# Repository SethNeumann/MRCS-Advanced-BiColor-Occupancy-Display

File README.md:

# REPO NAME:     MRCS-Advanced-BiColor-Occupancy-Display

## License: Creative Commons Attribution-NonCommercial-ShareAlike

The original board, which I designed for Allison Dendy had a pull up SIP (4.7K) and second SIP (nominally 470 ohms) on the common anode to limit
current. Depending on the 3 lead Red/Green LED used the Red was significantly brighter than the Green. Green/Red brightness is always an issue as 
about 20% of males have some red/green color weakness, so adjustment is very individual.

This version has an additional DIP resistor pack in series with the Red leads to further limit the Red brigtness. I used A 220 ohm SIP for the common
anode and 1K for the red. This made the Jameco 2266591 LED appear about as bright on each side to me.

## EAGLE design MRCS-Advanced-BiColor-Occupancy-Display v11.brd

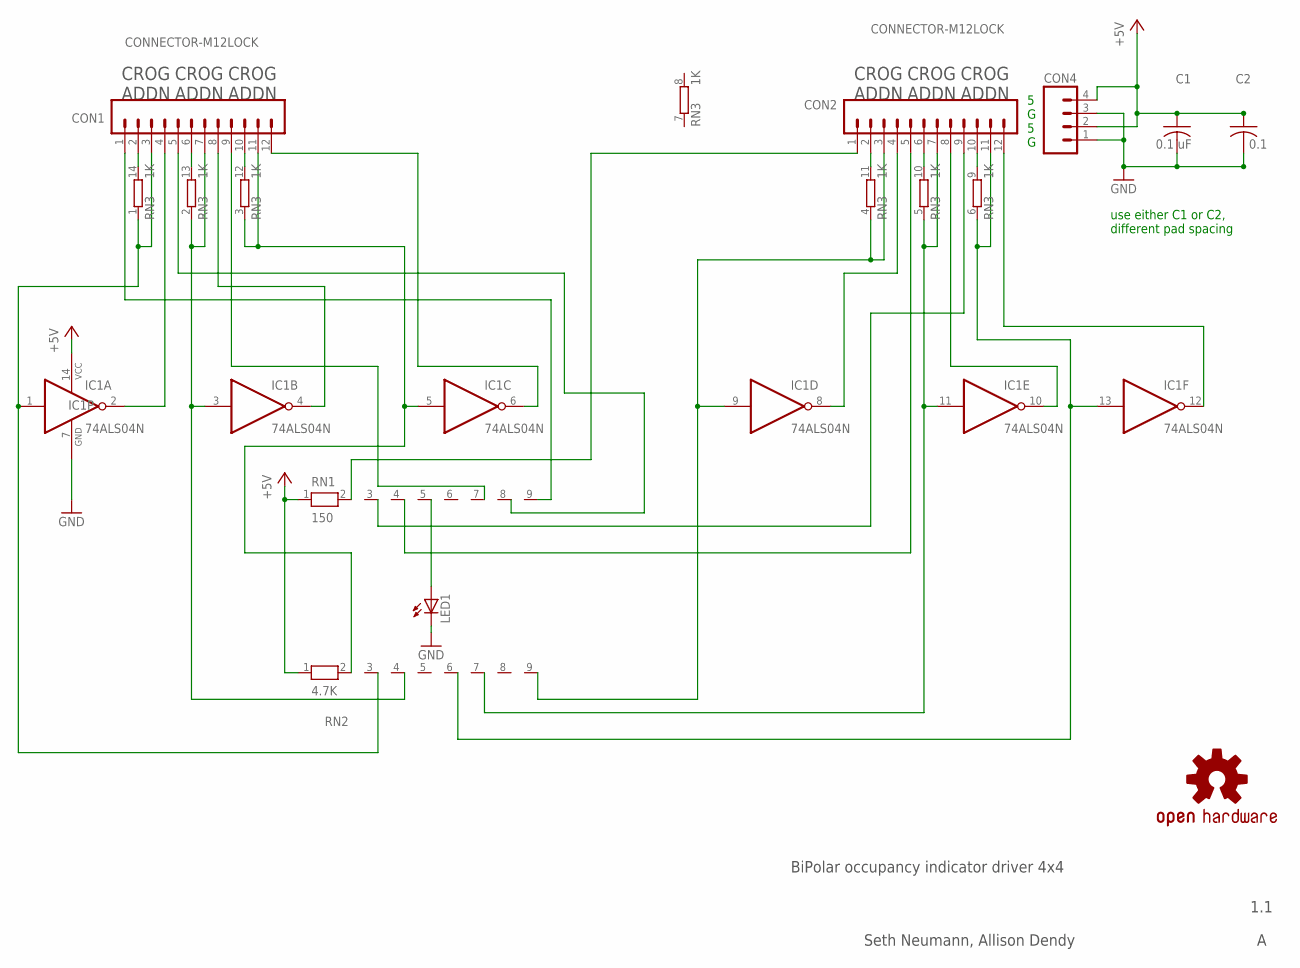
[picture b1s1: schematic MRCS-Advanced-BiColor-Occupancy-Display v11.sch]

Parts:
C1: 0.1 uF; C-PTH-0.100
C2: 0.1; C050-024X044
CON1, CON2: CONNECTOR-M12LOCK; 1X12_LOCK
CON4: CONNECTOR-M04SCREW; SCREWTERMINAL-3.5MM-4
IC1: 74ALS04N; DIL14
LED1: LEDLED3MM; LED3MM
OSHW1: DOC-OSHW-LOGO-M; OSHW-LOGO-M
RN1: 150; RN-9
RN2: 4.7K; RN-9
RN3: 1K; DIL14

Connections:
GND: C1.2, C2.2, CON4.1, CON4.3, IC1.7 (GND), LED1.K (C)
unnamed: CON1.2, RN3.14 (2)
unnamed: CON1.11, IC1.5 (I), RN2.2, RN3.3 (1)
unnamed: CON1.1, RN1.9
unnamed: CON1.4, IC1.2 (O)
unnamed: CON1.7, IC1.3 (I), RN2.4, RN3.2 (1)
unnamed: CON1.12, IC1.6 (O)
unnamed: CON1.8, IC1.4 (O)
unnamed: CON1.5, RN1.8
unnamed: CON2.3, IC1.9 (I), RN2.9, RN3.4 (1)
unnamed: CON1.9, RN1.7
unnamed: CON2.8, IC1.10 (O)
unnamed: CON2.12, IC1.12 (O)
unnamed: CON2.4, IC1.8 (O)
unnamed: CON2.1, RN1.2
unnamed: CON2.5, RN1.4
unnamed: CON1.3, IC1.1 (I), RN2.3, RN3.1
unnamed: LED1.A, RN1.5
unnamed: CON2.7, IC1.11 (I), RN2.7, RN3.5 (1)
unnamed: CON2.9, RN1.3
unnamed: CON2.11, IC1.13 (I), RN2.6, RN3.6 (1)
unnamed: CON1.6, RN3.13 (2)
unnamed: CON1.10, RN3.12 (2)
unnamed: CON2.2, RN3.11 (2)
unnamed: CON2.6, RN3.10 (2)
unnamed: CON2.10, RN3.9 (2)
VCC: C1.1, C2.1, CON4.2, CON4.4, IC1.14 (VCC), RN1.1, RN2.1

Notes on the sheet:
BiPolar occupancy indicator driver 4x4
1.1
Seth Neumann, Allison Dendy
CROG ADDN
5 G 5 G
use either C1 or C2, different pad spacing

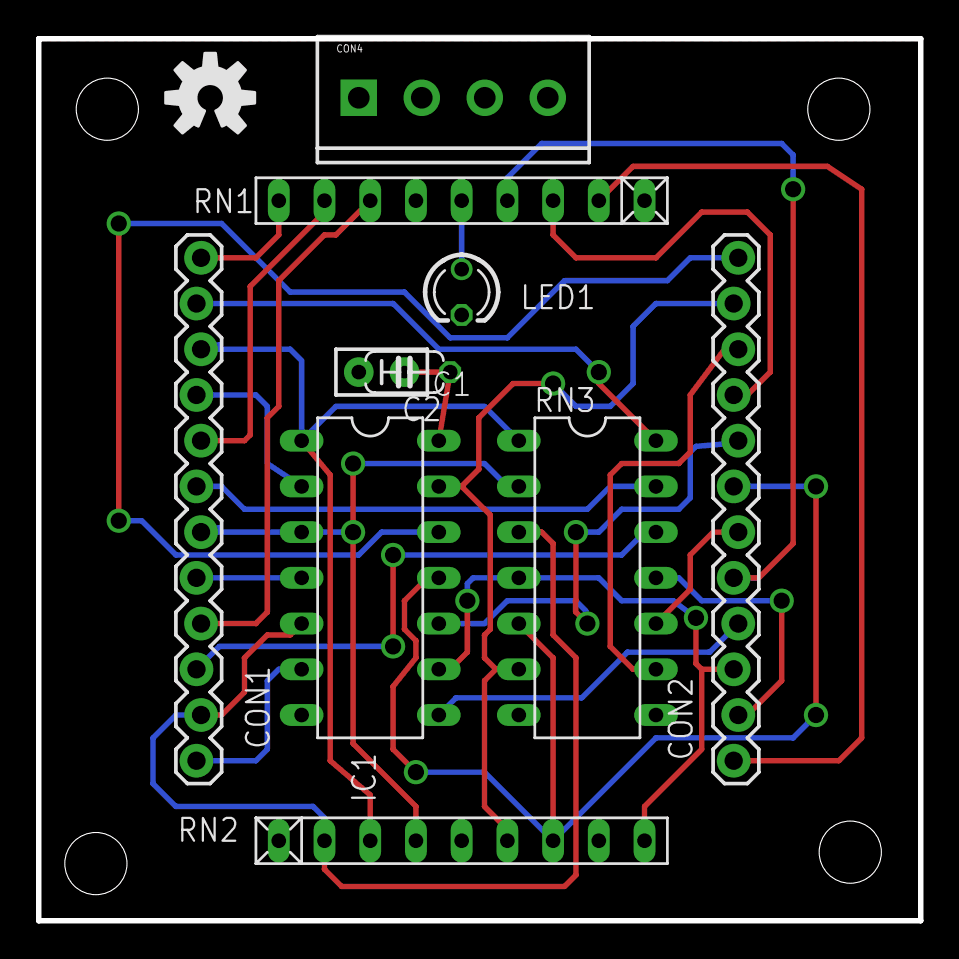
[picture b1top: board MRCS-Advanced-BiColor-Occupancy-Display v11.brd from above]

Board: 2 copper layers, 49.0 x 49.0 mm, 13 parts (0 on the bottom side), 27 nets.

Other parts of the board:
U$1: CA-PROP65WARNING
U$2: MRCSLOGOBTM

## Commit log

2023-11-30 Update DESCRIPTION
2023-11-30 Update INFO
2023-11-30 imported work files into GitHub
    moving work files around to clean up documentation

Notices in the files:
parts and their libraries:
SPCoast: http://freedomdefined.org/OSHW Creative Commons - Attribution - ShareAlike 3.0
